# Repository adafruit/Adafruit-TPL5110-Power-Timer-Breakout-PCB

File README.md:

## Adafruit TPL5110 Power Timer Breakout PCB

<a href="http://www.adafruit.com/products/3435"><br/>
Click here to purchase one from the Adafruit shop</a>

PCB files for the Adafruit TPL5110 Power Timer Breakout. For more details, Pick up one today & check out the product page at
* https://www.adafruit.com/products/3435

### Description

With some development boards, low power usage is an afterthought. Especially when price and usability is the main selling point. So what should you do when it's time to turn around and make that project of yours run on a battery or solar? Sure you could try to hot-air that regulator off, or you could jerry-rig a relay. Or, use a 555? Ugh, the options aren't that great.

The Adafruit TPL5110 Power Timer is a stand-alone breakout that will turn any electronics into low-power electronics! It will take care of turning your project on/off using a built in timer that can vary from once every 100ms up to once every two hours. Basically, the TPL will turn on periodically, adjustable by potentiometer or resistor, and turn on your project's power. It will then wait until a signal is received from the project to tell the TPL that it can safely turn off the power. If the TPL does not receive a signal by the set time-out, it will reset the device like a watchdog timer.

Usage is easy. First, set your desired delay by adjusting the on-board trim pot: nearly-all-the-way-to-the-left is "once per 100ms" and all-the-way-to-the-right is "once every 2 hours". Then, connect VDD up to your 3-5V power supply and then your project's power-in to the Drive pin. Finally, select a signal pin from your project to the Done pin. In your project's code or design, just make sure that it sets the Done pin high once it is completed with its task. That's it!

While the TPL5110 is running (but the remainder of the project is de-powered) the current draw is about 20uA (according to our Monsoon Power Meter).

If you want to turn the device on by hand, you can also activate the TPL by pressing the onboard tactile switch (or wire your own switch to the Delay pin). See? Your power problems just got solved!

While we've used this breakout with Huzzah ESP8266 Feather successfully - other people have said it doesn't work for them. So use with ESP8266 is not guaranteed.

Comes as a fully assembled breakout board with a TPL5110 chip, all components on-board, and some header. A little light soldering is required to put it together for breadboard use.

### License

Adafruit invests time and resources providing this open source design, please support Adafruit and open-source hardware by purchasing products from [Adafruit](https://www.adafruit.com)!

Designed by Limor Fried/Ladyada for Adafruit Industries.

Creative Commons Attribution/Share-Alike, all text above must be included in any redistribution. See license.txt for additional details.

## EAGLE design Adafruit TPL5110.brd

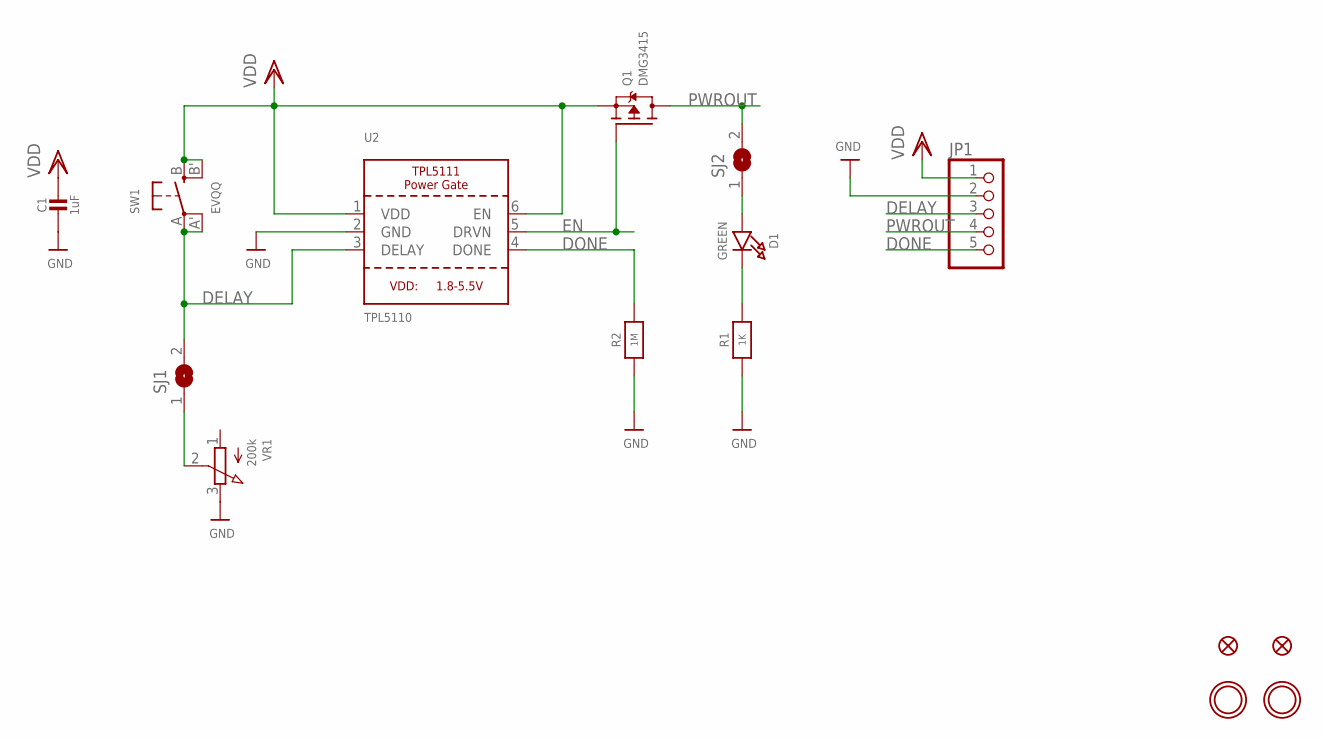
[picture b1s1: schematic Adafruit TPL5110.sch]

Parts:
C1: 1uF; 0805-NO
D1: GREEN; CHIPLED_0805_NOOUTLINE
FID1, FID2: FIDUCIAL""; FIDUCIAL_1MM
JP1: HEADER-1X570MIL; 1X05_ROUND_70
Q1: DMG3415; SOT23-WIDE
R1: 1K; 0805-NO
R2: 1M; 0805-NO
SJ1, SJ2: SOLDERJUMPERCLOSED; SOLDERJUMPER_CLOSEDWIRE
SW1: EVQQ; EVQ-Q2_SMALLER
U2: TPL5110; SOT23-6
U$7, U$8: MOUNTINGHOLE2.5; MOUNTINGHOLE_2.5_PLATED
VR1: 200k; TRIMPOT_BOURNS_TC33X-2

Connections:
DELAY: JP1.3, SJ1.2, SW1.A, SW1.A' (P1), U2.3 (DELAY)
DONE: JP1.5, R2.2, U2.4 (DONE)
EN: Q1.1 (G), U2.5 (DRVN)
GND: C1.2, JP1.2, R1.1, R2.1, U2.2 (GND), VR1.3 (E)
unnamed: SJ1.1, VR1.2 (S)
unnamed: D1.A, SJ2.1
unnamed: D1.C, R1.2
PWROUT: JP1.4, Q1.3 (D), SJ2.2
VDD: C1.1, JP1.1, Q1.2 (S), SW1.B (S), SW1.B' (S1), U2.1 (VDD), U2.6 (EN)

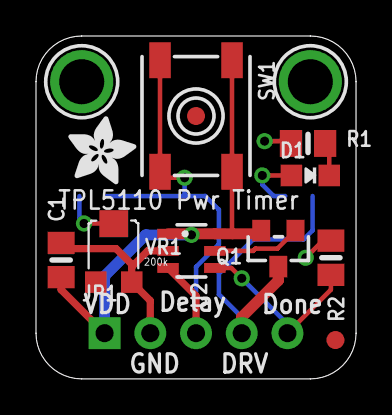
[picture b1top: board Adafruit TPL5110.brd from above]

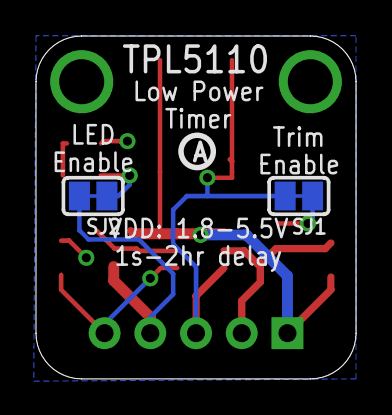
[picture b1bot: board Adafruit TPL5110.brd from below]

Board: 2 copper layers, 17.8 x 19.1 mm, 17 parts (3 on the bottom side), 9 nets.

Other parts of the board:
U$5: ADAFRUIT_3.5MM
U$11: PCBFEAT-REV-040

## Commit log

2017-03-01 init
